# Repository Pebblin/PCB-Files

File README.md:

# PCB-Files
Contains KiCad PCB files used for various projects

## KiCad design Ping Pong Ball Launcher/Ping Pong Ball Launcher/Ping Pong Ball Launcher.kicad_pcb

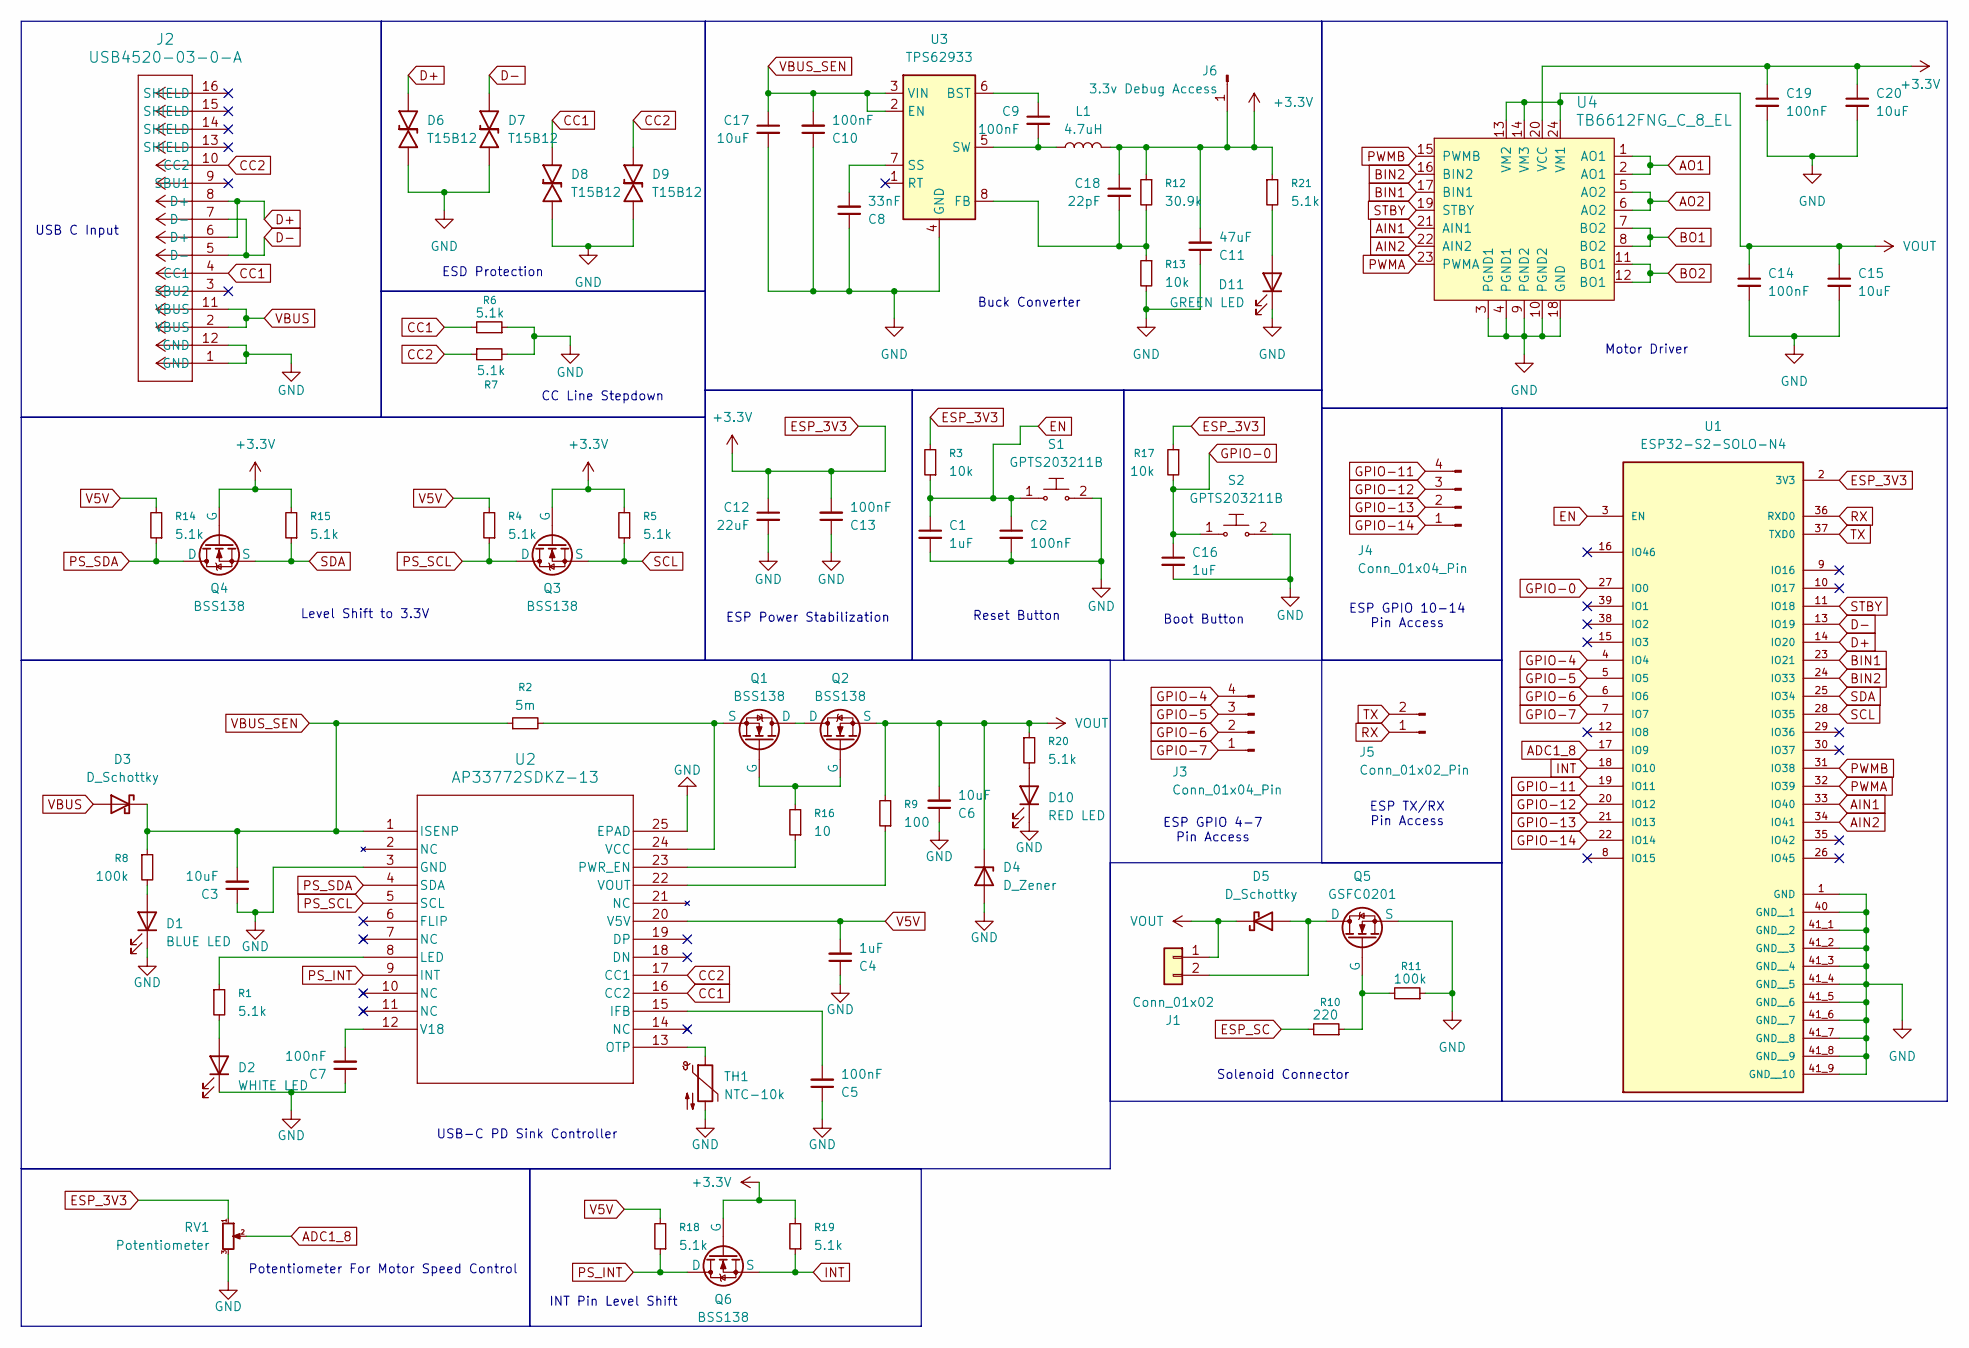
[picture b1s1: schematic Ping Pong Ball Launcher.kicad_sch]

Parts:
C1, C4, C16: 1uF; C_0603_1608Metric_Pad1.08x0.95mm_HandSolder
C2, C5, C7, C9, C10, C13, C14, C19: 100nF; C_0603_1608Metric_Pad1.08x0.95mm_HandSolder
C3, C6, C15, C17, C20: 10uF; C_0603_1608Metric_Pad1.08x0.95mm_HandSolder
C8: 33nF; C_0603_1608Metric_Pad1.08x0.95mm_HandSolder
C11: 47uF; C_0805_2012Metric_Pad1.18x1.45mm_HandSolder
C12: 22uF; C_0603_1608Metric_Pad1.08x0.95mm_HandSolder
C18: 22pF; C_0603_1608Metric_Pad1.08x0.95mm_HandSolder
D1: BLUE LED; LED
D2: WHITE LED; LED
D3, D5: D_Schottky; D_DO-201AD_P12.70mm_Horizontal
D4: D_Zener; D_SMB
D6, D7, D8, D9: T15B12; D_SMB
D10: RED LED; LED
D11: GREEN LED; LED
J1: Conn_01x02
J2: USB4520-03-0-A
J3, J4: Conn_01x04_Pin
J5: Conn_01x02_Pin
J6: 3.3v Debug Access
L1: 4.7uH; CB2518T4R7MR
Q1, Q2, Q3, Q4, Q6: BSS138; SOT-23-3
Q5: GSFC0201; SOT-23-3
R1, R4, R5, R6, R7, R14, R15, R18, R19, R20, R21: 5.1k; R_0603_1608Metric_Pad0.98x0.95mm_HandSolder
R2: 5m; R_1206_3216Metric_Pad1.30x1.75mm_HandSolder
R3, R13, R17: 10k; R_0603_1608Metric_Pad0.98x0.95mm_HandSolder
R8, R11: 100k; R_0805_2012Metric_Pad1.20x1.40mm_HandSolder
R9: 100; R_0603_1608Metric_Pad0.98x0.95mm_HandSolder
R10: 220; R_0603_1608Metric_Pad0.98x0.95mm_HandSolder
R12: 30.9k; R_0603_1608Metric_Pad0.98x0.95mm_HandSolder
R16: 10; R_0603_1608Metric_Pad0.98x0.95mm_HandSolder
RV1: Potentiometer; 3310Y
S1, S2: GPTS203211B; PushButton_12x12mm_THT_GPTS203211B; MPN GPTS203211B; Digi-Key_PN CW181-ND
TH1: NTC-10k; NC20K00103KBA
U1: ESP32-S2-SOLO-N4; XCVR_ESP32-S2-SOLO-N4; PARTREV 1.6
U2: AP33772SDKZ-13; AP33772DKZ
U3: TPS62933; SOT-583-8
U4: TB6612FNG_C_8_EL; LSSOP-24_W5.6mm; MPN TB6612FNG,C,8,EL; Digi-Key_PN TB6612FNGC8ELCT-ND

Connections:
ADC1_8: RV1.2, U1.17 (IO9)
AIN1: U1.33 (IO40), U4.21 (AIN1)
AIN2: U1.34 (IO41), U4.22 (AIN2)
AO1: U4.1 (AO1), U4.2 (AO1)
AO2: U4.5 (AO2), U4.6 (AO2)
BIN1: U1.23 (IO21), U4.17 (BIN1)
BIN2: U1.24 (IO33), U4.16 (BIN2)
BO1: U4.7 (BO2), U4.8 (BO2)
BO2: U4.11 (BO1), U4.12 (BO1)
CC1: D8.2 (A2), J2.4 (CC1), R6.2, U2.16 (CC2)
CC2: D9.2 (A2), J2.10 (CC2), R7.1, U2.17 (CC1)
D+: D6.2 (A2), J2.6 (D+), J2.8 (D+), U1.14 (IO20)
D-: D7.2 (A2), J2.5 (D-), J2.7 (D-), U1.13 (IO19)
EN: C1.1, C2.1, R3.1, S1.1, U1.3 (EN)
ESP_3V3: C11.2, C12.1, C13.2, C18.1, C19.1, C20.1, J6.1, L1.2, Q3.2 (G), Q4.2 (G), Q6.2 (G), R3.2, R5.2, R12.1, R15.2, R17.1, R19.2, R21.1, RV1.1, U1.2 (3V3), U4.20 (VCC)
ESP_SC: R10.2
GND: C1.2, C2.2, C3.1, C4.1, C5.1, C6.1, C7.1, C8.1, C10.1, C11.1, C12.2, C13.1, C14.2, C15.2, C16.2, C17.2, C19.2, C20.2, D1.1 (K), D2.1 (K), D4.2 (A), D6.1 (A1), D7.1 (A1), D8.1 (A1), D9.1 (A1), D10.1 (K), D11.1 (K), J2.1 (GND), J2.12 (GND), Q5.3 (S), R6.1, R7.2, R11.1, R13.2, RV1.3, S1.2, S2.2, TH1.2, U1.1 (GND), U1.40 (GND__1), U1.41_1 (GND__2), U1.41_2 (GND__3), U1.41_3 (GND__4), U1.41_4 (GND__5), U1.41_5 (GND__6), U1.41_6 (GND__7), U1.41_7 (GND__8), U1.41_8 (GND__9), U1.41_9 (GND__10), U2.3 (GND), U2.25 (EPAD), U3.4 (GND), U4.3 (PGND1), U4.4 (PGND1), U4.9 (PGND2), U4.10 (PGND2), U4.18 (GND)
GPIO-0: C16.1, R17.2, S2.1, U1.27 (IO0)
GPIO-4: J3.4, U1.4 (IO4)
GPIO-5: J3.3, U1.5 (IO5)
GPIO-6: J3.2, U1.6 (IO6)
GPIO-7: J3.1, U1.7 (IO7)
GPIO-11: J4.4, U1.19 (IO11)
GPIO-12: J4.3, U1.20 (IO12)
GPIO-13: J4.2, U1.21 (IO13)
GPIO-14: J4.1, U1.22 (IO14)
INT: Q6.3 (S), R19.1, U1.18 (IO10)
unnamed: D1.2 (A), R8.2
unnamed: D2.2 (A), R1.2
unnamed: D5.2 (A), J1.2, Q5.1 (D)
unnamed: D10.2 (A), R20.2
unnamed: D11.2 (A), R21.2
unnamed: Q1.1 (D), Q2.1 (D)
unnamed: Q1.2 (G), Q2.2 (G), R16.2
unnamed: Q1.3 (S), R2.2, U2.24 (VCC)
unnamed: Q5.2 (G), R10.1, R11.2
unnamed: C5.2, U2.15 (IFB)
unnamed: R1.1, U2.8 (LED)
unnamed: TH1.1, U2.13 (OTP)
unnamed: R16.1, U2.23 (PWR_EN)
unnamed: C7.2, U2.12 (V18)
unnamed: R9.1, U2.22 (VOUT)
unnamed: C9.1, U3.6 (BST)
unnamed: C18.2, R12.2, R13.1, U3.8 (FB)
unnamed: C8.2, U3.7 (SS)
unnamed: C9.2, L1.1, U3.5 (SW)
PS_INT: Q6.1 (D), R18.1, U2.9 (INT)
PS_SCL: Q3.1 (D), R4.1, U2.5 (SCL)
PS_SDA: Q4.1 (D), R14.1, U2.4 (SDA)
PWMA: U1.32 (IO39), U4.23 (PWMA)
PWMB: U1.31 (IO38), U4.15 (PWMB)
RX: J5.1, U1.36 (RXD0)
SCL: Q3.3 (S), R5.1, U1.28 (IO35)
SDA: Q4.3 (S), R15.1, U1.25 (IO34)
STBY: U1.11 (IO18), U4.19 (STBY)
TX: J5.2, U1.37 (TXD0)
V5V: C4.2, R4.2, R14.2, R18.2, U2.20 (V5V)
VBUS: D3.2 (A), J2.2 (VBUS), J2.11 (VBUS)
VBUS_SEN: C3.2, C10.2, C17.1, D3.1 (K), R2.1, R8.1, U2.1 (ISENP), U3.2 (EN), U3.3 (VIN)
VOUT: C6.2, C14.1, C15.1, D4.1 (K), D5.1 (K), J1.1, Q2.3 (S), R9.2, R20.1, U4.13 (VM2), U4.14 (VM3), U4.24 (VM1)

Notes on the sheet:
Motor Driver
ESP GPIO 10-14 Pin Access
CC Line Stepdown
USB C Input
ESP GPIO 4-7 Pin Access
ESP TX/RX Pin Access
Buck Converter
ESD Protection
Solenoid Connector
Reset Button
Level Shift to 3.3V
INT Pin Level Shift
USB-C PD Sink Controller
Boot Button
ESP Power Stabilization
Potentiometer For Motor Speed Control

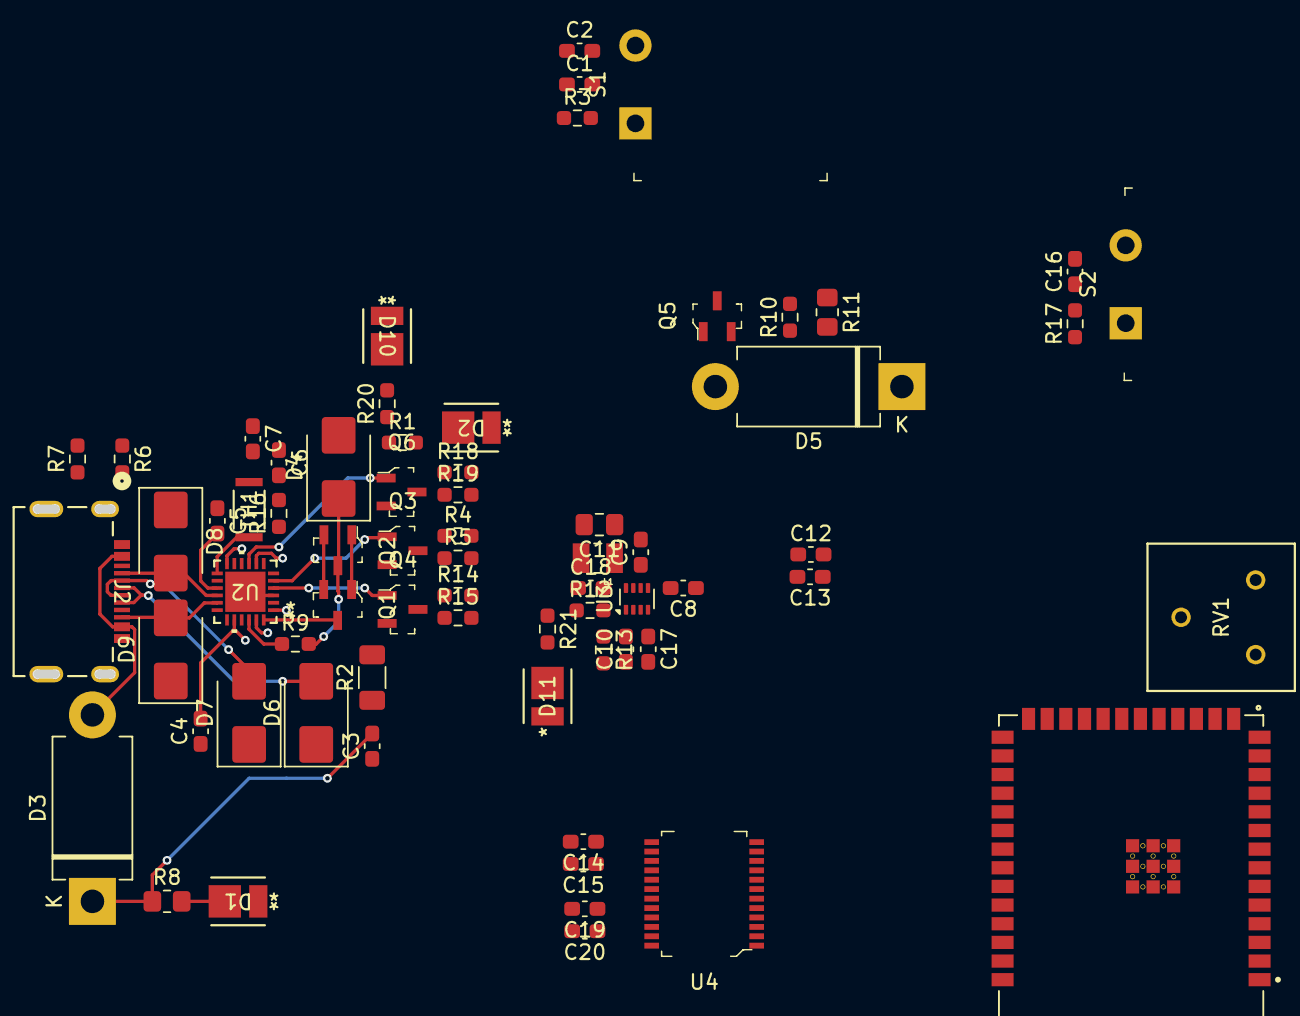
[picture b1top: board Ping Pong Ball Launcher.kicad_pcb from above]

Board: 2 copper layers, 68 parts (0 on the bottom side), 49 nets.

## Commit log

2025-05-23 Added ball launcher
